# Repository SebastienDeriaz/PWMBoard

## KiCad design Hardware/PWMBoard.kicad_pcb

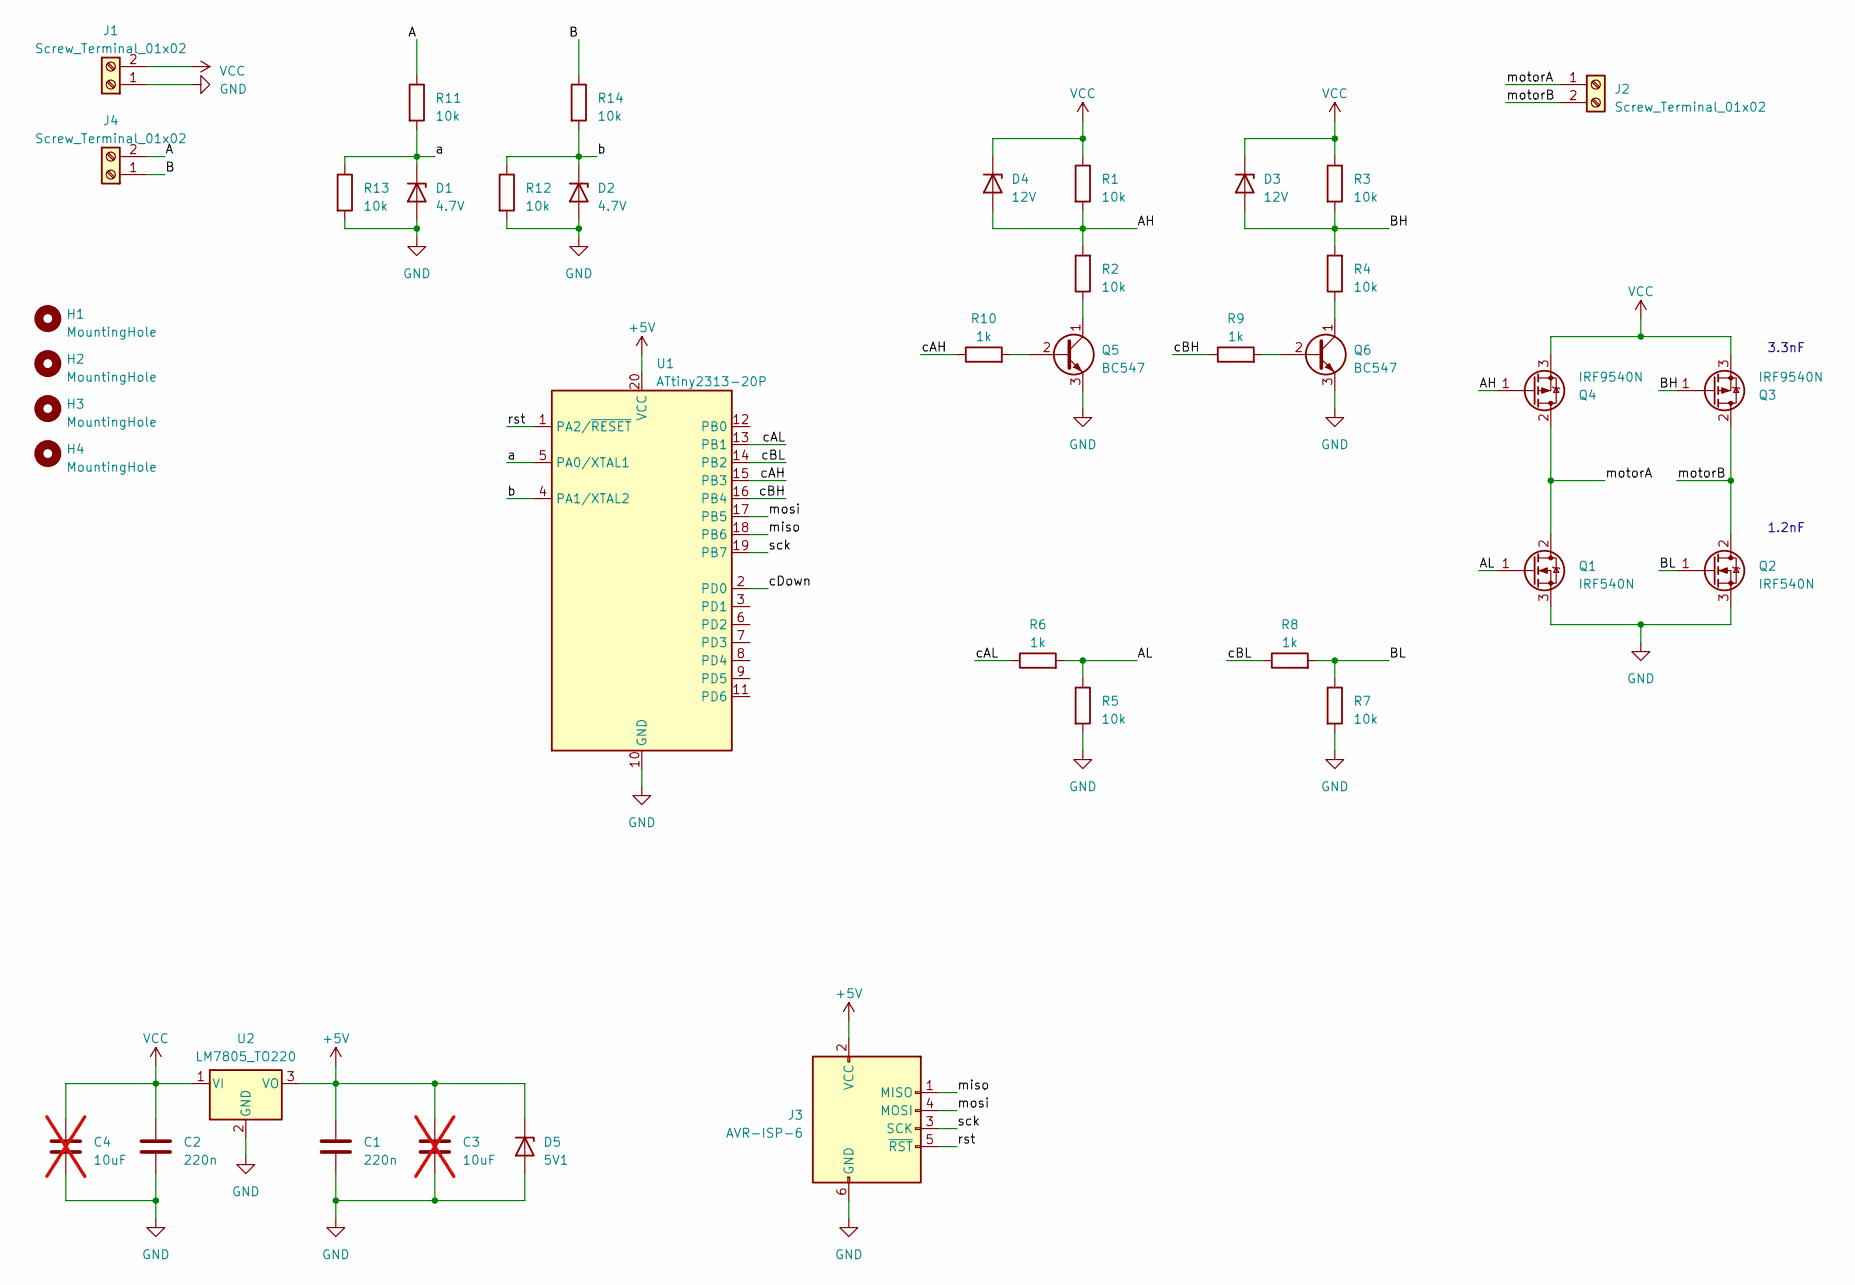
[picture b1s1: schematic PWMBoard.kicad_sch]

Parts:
C1, C2: 220n; C_Disc_D8.0mm_W2.5mm_P5.00mm
C3, C4: 10uF; C_Disc_D8.0mm_W2.5mm_P5.00mm; not fitted
D1, D2: 4.7V; D_T-1_P5.08mm_Horizontal
D3, D4: 12V; D_A-405_P5.08mm_Vertical_KathodeUp
D5: 5V1; D_A-405_P7.62mm_Horizontal
H1, H2, H3, H4: MountingHole; MountingHole_3.2mm_M3_DIN965
J1, J2, J4: Screw_Terminal_01x02; TerminalBlock_Phoenix_MKDS-3-2-5.08_1x02_P5.08mm_Horizontal
J3: AVR-ISP-6; IDC-Header_2x03_P2.54mm_Vertical
Q1, Q2: IRF540N; TO-220-3_Horizontal_TabDown
Q3, Q4: IRF9540N; TO-220-3_Horizontal_TabDown
Q5, Q6: BC547; TO-92_Inline_Wide
R1, R2, R3, R5, R12, R13, R14: 10k; R_Axial_DIN0207_L6.3mm_D2.5mm_P5.08mm_Vertical
R4, R7: 10k; R_Axial_DIN0207_L6.3mm_D2.5mm_P10.16mm_Horizontal
R6, R8, R10: 1k; R_Axial_DIN0207_L6.3mm_D2.5mm_P5.08mm_Vertical
R9: 1k; R_Axial_DIN0207_L6.3mm_D2.5mm_P2.54mm_Vertical
R11: 10k; R_Axial_DIN0207_L6.3mm_D2.5mm_P2.54mm_Vertical
U1: ATtiny2313-20P; DIP-20_W7.62mm
U2: LM7805_TO220; TO-220-3_Horizontal_TabDown

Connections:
+5V: C1.1, C3.1, D5.1 (K), J3.2 (VCC), U1.20 (VCC), U2.3 (VO)
/A: J4.2, R11.1
/AH: D4.2 (A), Q4.1 (G), R1.2, R2.2
/AL: Q1.1 (G), R5.1, R6.2
/B: J4.1, R14.1
/BH: D3.2 (A), Q3.1 (G), R3.2, R4.2
/BL: Q2.1 (G), R7.1, R8.2
/a: D1.1 (K), R11.2, R13.1, U1.5 (PA0/XTAL1)
/b: D2.1 (K), R12.1, R14.2, U1.4 (PA1/XTAL2)
/cAH: R10.1, U1.15 (PB3)
/cAL: R6.1, U1.13 (PB1)
/cBH: R9.1, U1.16 (PB4)
/cBL: R8.1, U1.14 (PB2)
/cDown: U1.2 (PD0)
/miso: J3.1 (MISO), U1.18 (PB6)
/mosi: J3.4 (MOSI), U1.17 (PB5)
/motorA: J2.1, Q1.2 (D), Q4.2 (D)
/motorB: J2.2, Q2.2 (D), Q3.2 (D)
/rst: J3.5 (~RST), U1.1 (PA2/~RESET)
/sck: J3.3 (SCK), U1.19 (PB7)
GND: C1.2, C2.2, C3.2, C4.2, D1.2 (A), D2.2 (A), D5.2 (A), J1.1, J3.6 (GND), Q1.3 (S), Q2.3 (S), Q5.3 (E), Q6.3 (E), R5.2, R7.2, R12.2, R13.2, U1.10 (GND), U2.2 (GND)
unnamed: Q5.2 (B), R10.2
unnamed: Q5.1 (C), R2.1
unnamed: Q6.2 (B), R9.2
unnamed: Q6.1 (C), R4.1
VCC: C2.1, C4.1, D3.1 (K), D4.1 (K), J1.2, Q3.3 (S), Q4.3 (S), R1.1, R3.1, U2.1 (VI)

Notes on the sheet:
1.2nF
3.3nF

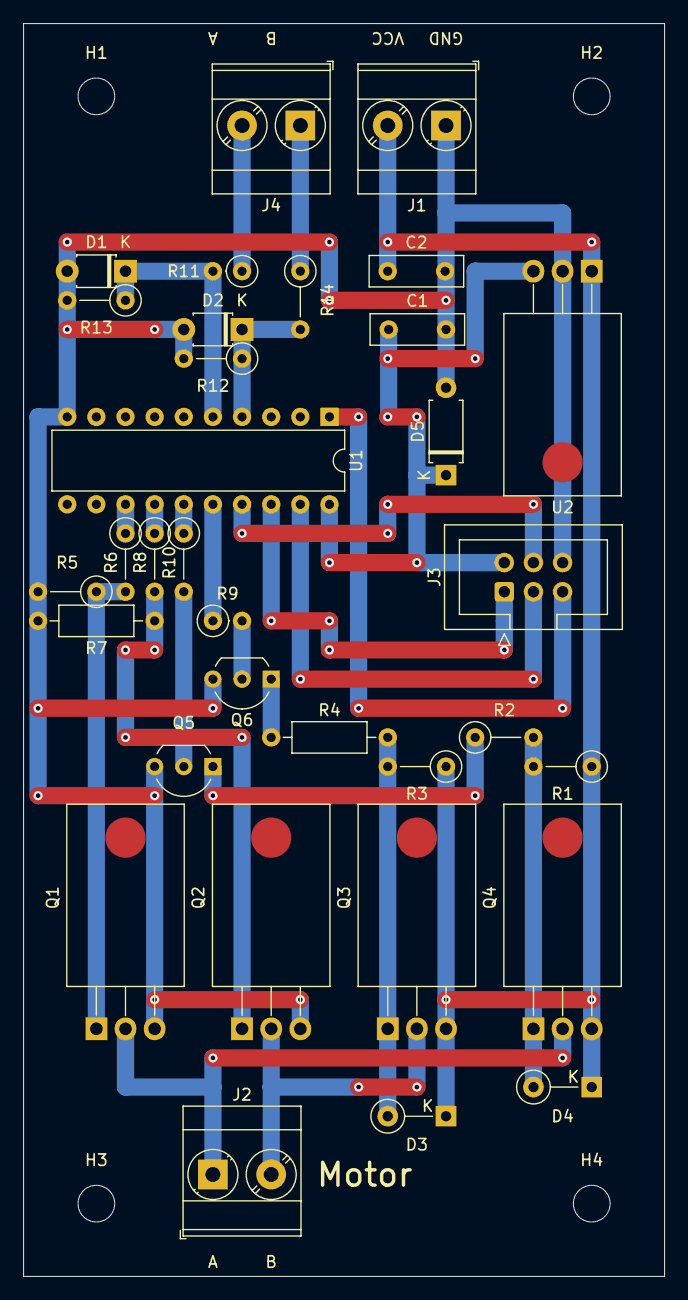
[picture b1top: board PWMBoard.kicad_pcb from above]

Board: 2 copper layers, 55.9 x 109.2 mm, 37 parts (0 on the bottom side), 25 nets.

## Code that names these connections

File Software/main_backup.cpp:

#include <avr/io.h>
#define F_CPU 8000000UL
#include <avr/iotn2313.h>
// #include <math.h>
// #include <stdint.h>
#include <util/delay.h>

class Pin {
    volatile uint8_t& _PORT;
    volatile uint8_t& _DDR;
    volatile uint8_t& _PIN;
    volatile uint8_t pin_number;
    void (*_enablePwm)(void) = nullptr;
    void (*_disablePwm)(void) = nullptr;
    void (*_setPwm)(uint16_t) = nullptr;
    bool pwmState = false;

   public:
    void setPwm(uint16_t value) {
        if (pwmState != (value != 0)) {
            if (value != 0) {
                pwmState = true;
                _enablePwm();
            } else {
                pwmState = false;
                _disablePwm();
            }
        }
        _setPwm(value);
    }

    Pin(volatile uint8_t& port, volatile uint8_t& ddr, volatile uint8_t& pin,
        uint8_t pin_number, void (*enablePwm)(void) = nullptr,
        void (*disablePwm)(void) = nullptr, void (*setPwm)(uint16_t) = nullptr)
        : _PORT(port),
          _DDR(ddr),
          _PIN(pin),
          pin_number(pin_number),
          _enablePwm(enablePwm),
          _disablePwm(disablePwm),
          _setPwm(setPwm){};

    enum Direction { INPUT, OUTPUT, INPUT_PULLUP };
    void setDirection(Direction direction) {
        switch (direction) {
            case INPUT:
                _DDR &= ~(1 << pin_number);
                _PORT &= ~(1 << pin_number);
                break;
            case OUTPUT:
                _DDR |= (1 << pin_number);
                _PORT &= ~(1 << pin_number);
                break;
            case INPUT_PULLUP:
                _DDR &= ~(1 << pin_number);
                _PORT |= (1 << pin_number);
                break;
        }
    }

    bool getState() { return (_DDR & (1 << pin_number)) == 0; }
    void setState(bool value) {
        _PORT = (_PORT & ~(1 << pin_number)) | ((value ? 1 : 0) << pin_number);
    }
};

class SoftHBridge {
    float x;
    const float step = 1e-3;
    Pin& _AL;
    Pin& _BL;
    Pin& _AH;
    Pin& _BH;
    uint16_t ocrMax;

    public:
    void setDirection(float x) {
        if (x > 1.0f) {
            x = 1.0f;
        } else if (x < -1.0f) {
            x = -1.0f;
        }

        //uint16_t pwmValue = fabsf(x) * ocrMax;

        if (x >= 0.0f) {
            _AH.setPwm((uint16_t)x * ocrMax);
            _BH.setPwm(0);
            _AL.setState(false);
            _BL.setState(true);
        } else {
            _AH.setPwm(0);
            _BH.setPwm((uint16_t) - x * ocrMax);
            _AL.setState(true);
            _BL.setState(false);
        }

        /*if (x == 0.0f) {
            _AH.setPwm(pwmValue);
            _BH.setPwm(0);
            _AL.setState(false);
            _BL.setState(false);
        } else if (x > 0.0f) {
            _AH.setPwm(pwmValue);
            _BH.setPwm(0);
            _AL.setState(false);
            _BL.setState(true);
        } else {
            _AH.setPwm(0);
            _BH.setPwm(pwmValue);
            _AL.setState(true);
            _BL.setState(false);
        }*/
    }

   public:
    SoftHBridge(Pin& AL, Pin& BL, Pin& AH, Pin& BH, uint16_t ocrMax)
        : _AL(AL), _BL(BL), _AH(AH), _BH(BH), ocrMax(ocrMax) {
        _AL.setDirection(Pin::OUTPUT);
        _BL.setDirection(Pin::OUTPUT);
        _AH.setDirection(Pin::OUTPUT);
        _BH.setDirection(Pin::OUTPUT);
        _AL.setState(false);
        _BL.setState(false);
        _AH.setPwm(0);
        _BH.setPwm(0);
        x = 0.0f;
    }

    void update(bool A, bool B) {
        /*if (A) {
            x += step;
            if (x > 1.0f) {
                x = 1.0f;
            }
        } else if (B) {
            x -= step;
            if (x < 1.0f) {
                x = -1.0f;
            }
        } else {
            // If it is close to zero, make it zero
            if (fabsf(x) <= step) {
                x = 0.0f;
            } else if (x > 0) {
                x -= step;
            } else if (x < 0) {
                x += step;
            }
        }*/

        //setDirection(x);

        if (A) {
          setDirection(0.5);
        }
        else {
          setDirection(0.5);
        }
    }
};

int main(void) {
    /*   Configure Timer1   */
    // Set waveform generation mode to normal (TOP at 0xFFFF)
    TCCR1A = (0 << WGM10) | (1 << WGM11);
    // Set clock source to clk/1 (8MHz with 16 bits -> 122 Hz)
    TCCR1B =
        (1 << WGM13) | (1 << WGM12) | (0 << CS12) | (0 << CS11) | (1 << CS10);

    ICR1 = 2000;

    Pin BH(
        PORTB, DDRB, PINB, PB4,
        []() { TCCR1A |= (1 << COM1B1); },     // enable PWM
        []() { TCCR1A &= ~(1 << COM1B1); },    // disable PWM
        [](uint16_t value) { OCR1B = value; }  // set PWM
    );
    Pin AH(
        PORTB, DDRB, PINB, PB3,
        []() { TCCR1A |= (1 << COM1A1); },     // enable PWM
        []() { TCCR1A &= ~(1 << COM1A1); },    // disable PWM
        [](uint16_t value) { OCR1A = value; }  // set PWM
    );
    Pin BL(PORTB, DDRB, PINB, PB2);
    Pin AL(PORTB, DDRB, PINB, PB1);

    //Pin A(PORTA, DDRA, PINA, PA1);
    //Pin B(PORTA, DDRA, PINA, PA0);

    //A.setDirection(Pin::INPUT_PULLUP);
    //B.setDirection(Pin::INPUT_PULLUP);

    SoftHBridge softHBridge(AL, BL, AH, BH, ICR1);

    // SoftHBridge softHBridge(hbridge);

    softHBridge.setDirection(0.5);

    while (1) {
        /*softHBridge.update(
          false,//A.getState(),
          false
          //B.getState()
        );*/
        _delay_ms(1);
    }
}

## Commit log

2023-05-13 Working compile + flash
2023-05-21 Update PCB
2023-05-21 Update compile/flash scripts
2023-05-21 Update gitignore
2023-05-21 Update software
